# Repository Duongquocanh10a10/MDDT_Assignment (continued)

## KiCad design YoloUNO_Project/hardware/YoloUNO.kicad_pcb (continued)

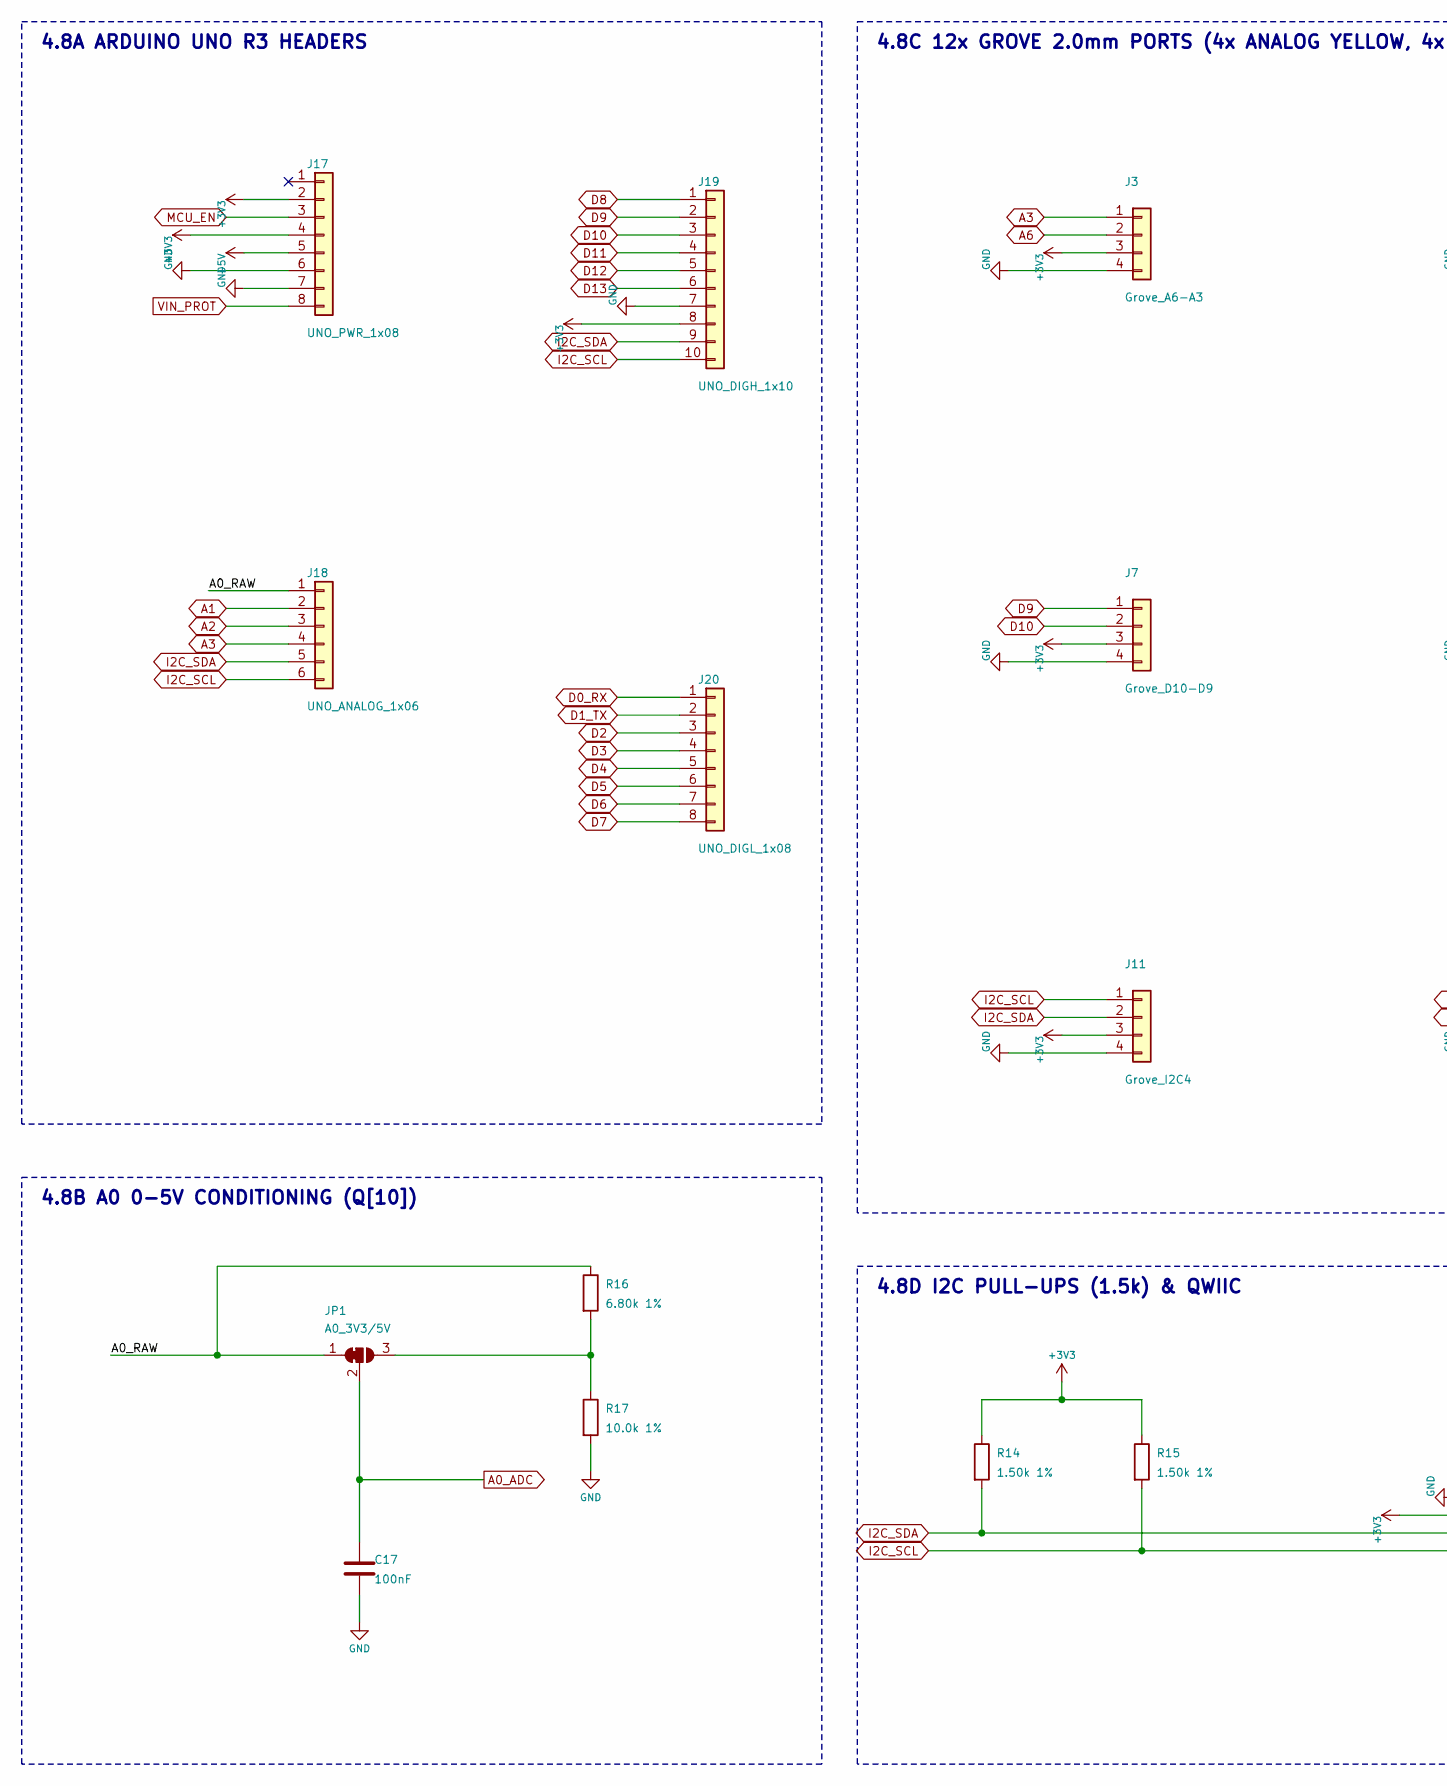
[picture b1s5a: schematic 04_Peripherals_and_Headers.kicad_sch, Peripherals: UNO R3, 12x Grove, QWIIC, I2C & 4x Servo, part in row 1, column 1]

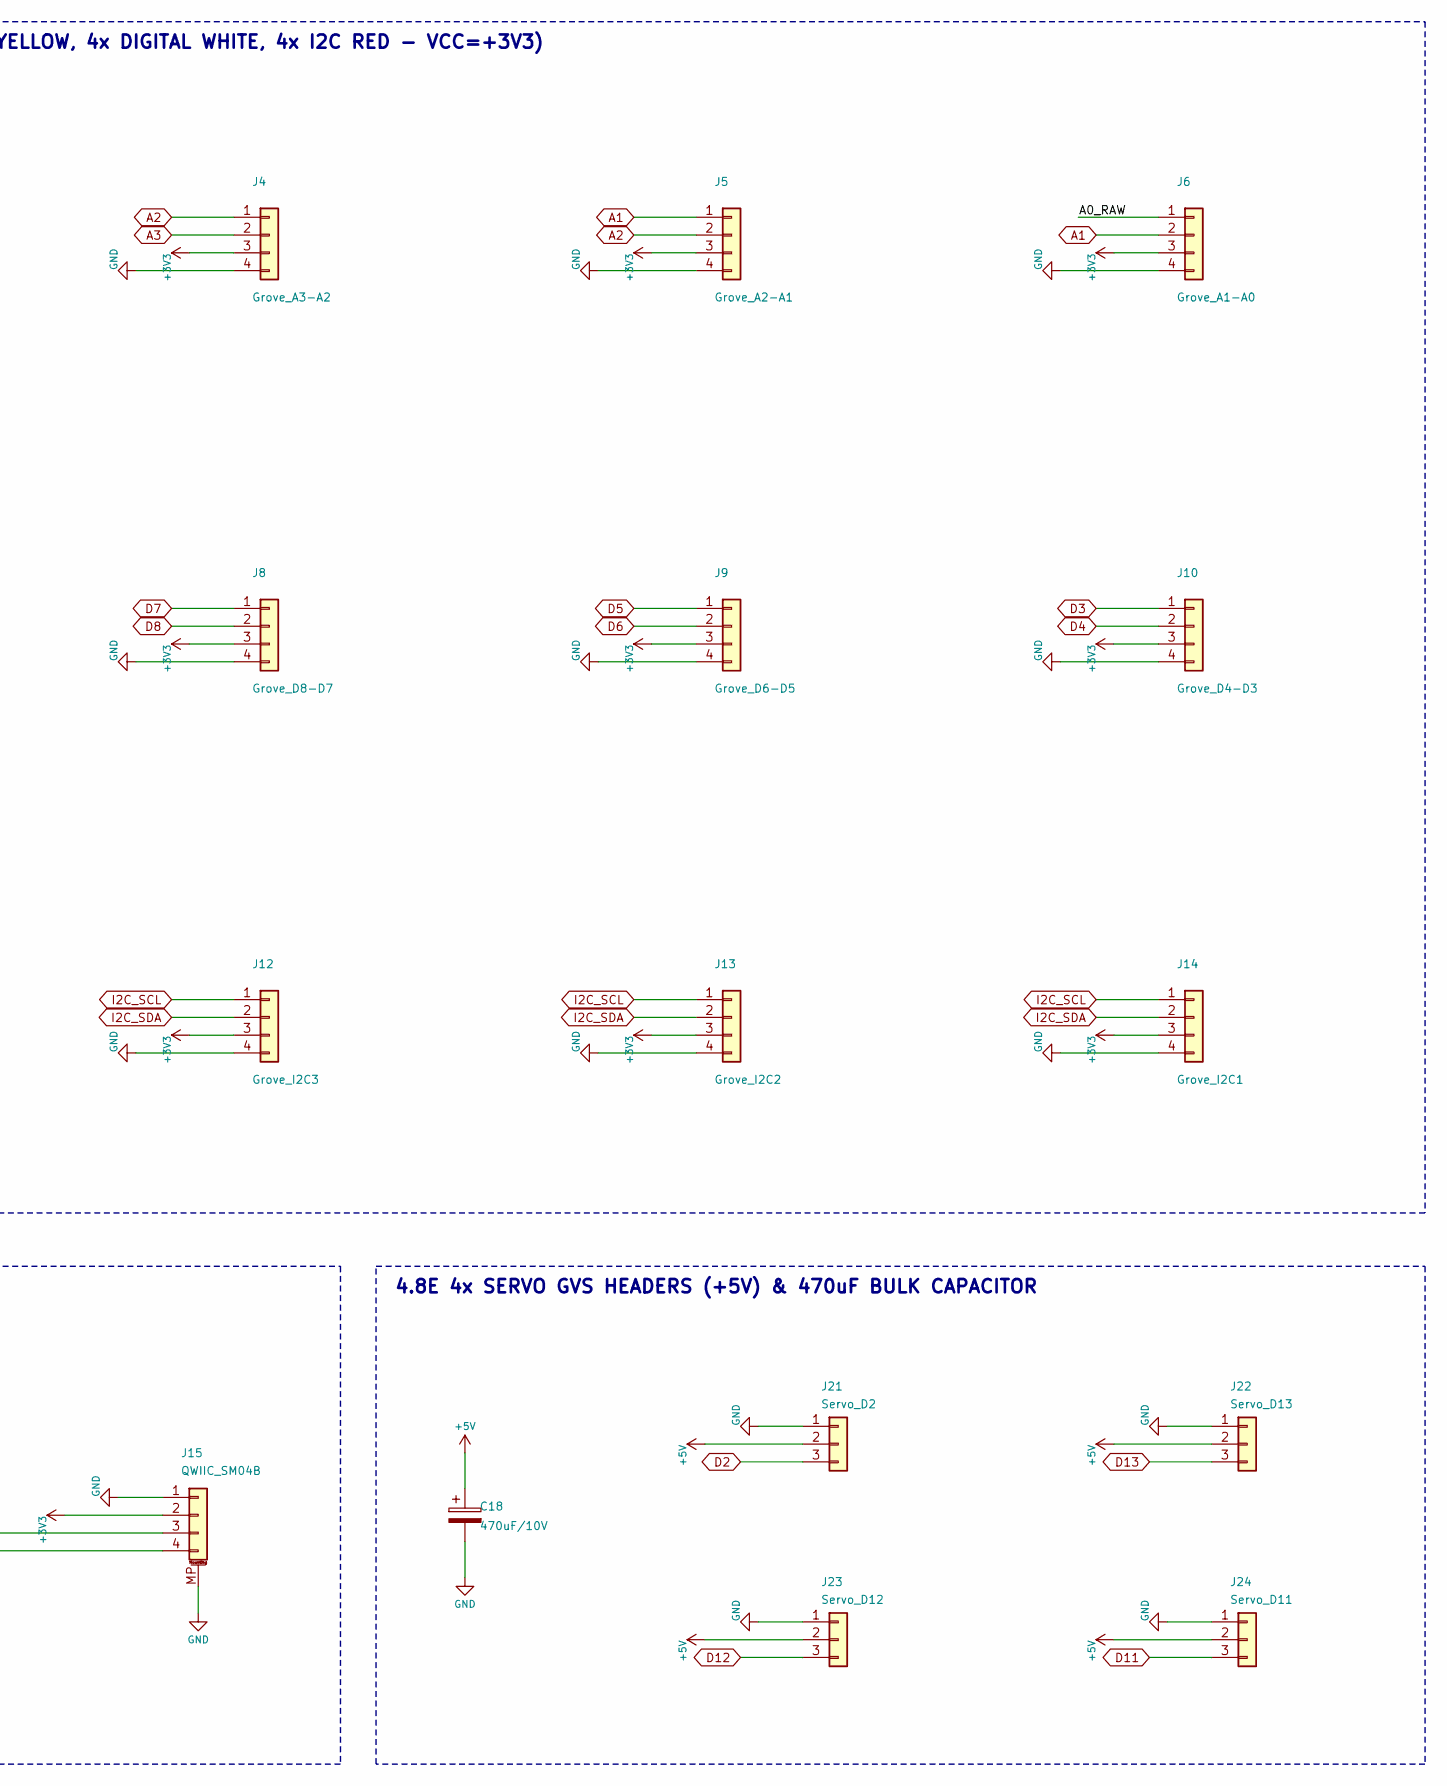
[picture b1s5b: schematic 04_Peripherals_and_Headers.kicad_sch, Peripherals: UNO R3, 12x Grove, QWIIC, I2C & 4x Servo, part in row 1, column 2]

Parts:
C17: 100nF; C_0603_1608Metric; MPN CL10B104KB8NNNC; LCSC C1591
C18: 470uF/10V; CP_Elec_8x10.5; MPN EEE-FK1A471P; LCSC C134734
J3: Grove_A6-A3; NS-Tech_Grove_1x04_P2mm_Vertical; MPN 110990030; LCSC C2906423
J4: Grove_A3-A2; NS-Tech_Grove_1x04_P2mm_Vertical; MPN 110990030; LCSC C2906423
J5: Grove_A2-A1; NS-Tech_Grove_1x04_P2mm_Vertical; MPN 110990030; LCSC C2906423
J6: Grove_A1-A0; NS-Tech_Grove_1x04_P2mm_Vertical; MPN 110990030; LCSC C2906423
J7: Grove_D10-D9; NS-Tech_Grove_1x04_P2mm_Vertical; MPN 112060001; LCSC C492401
J8: Grove_D8-D7; NS-Tech_Grove_1x04_P2mm_Vertical; MPN 112060001; LCSC C492401
J9: Grove_D6-D5; NS-Tech_Grove_1x04_P2mm_Vertical; MPN 112060001; LCSC C492401
J10: Grove_D4-D3; NS-Tech_Grove_1x04_P2mm_Vertical; MPN 112060001; LCSC C492401
J11: Grove_I2C4; NS-Tech_Grove_1x04_P2mm_Vertical; MPN 110990031; LCSC C2906424
J12: Grove_I2C3; NS-Tech_Grove_1x04_P2mm_Vertical; MPN 110990031; LCSC C2906424
J13: Grove_I2C2; NS-Tech_Grove_1x04_P2mm_Vertical; MPN 110990031; LCSC C2906424
J14: Grove_I2C1; NS-Tech_Grove_1x04_P2mm_Vertical; MPN 110990031; LCSC C2906424
J15: QWIIC_SM04B; JST_SH_SM04B-SRSS-TB_1x04-1MP_P1.00mm_Horizontal; MPN SM04B-SRSS-TB; LCSC C160404
J17: UNO_PWR_1x08; PinSocket_1x08_P2.54mm_Vertical; MPN FH-254-1x08; LCSC C49661
J18: UNO_ANALOG_1x06; PinSocket_1x06_P2.54mm_Vertical; MPN FH-254-1x06; LCSC C49659
J19: UNO_DIGH_1x10; PinSocket_1x10_P2.54mm_Vertical; MPN FH-254-1x10; LCSC C49663
J20: UNO_DIGL_1x08; PinSocket_1x08_P2.54mm_Vertical; MPN FH-254-1x08; LCSC C49661
J21: Servo_D2; PinHeader_1x03_P2.54mm_Vertical; MPN X6511WV-1x3; LCSC C492405
J22: Servo_D13; PinHeader_1x03_P2.54mm_Vertical; MPN X6511WV-1x3; LCSC C492405
J23: Servo_D12; PinHeader_1x03_P2.54mm_Vertical; MPN X6511WV-1x3; LCSC C492405
J24: Servo_D11; PinHeader_1x03_P2.54mm_Vertical; MPN X6511WV-1x3; LCSC C492405
JP1: A0_3V3/5V; SolderJumper-3_P1.3mm_Bridged12_Pad1.0x1.5mm; MPN SJ-3-1.3MM; LCSC N/A
R14, R15: 1.50k 1%; R_0603_1608Metric; MPN RC0603FR-071K5L; LCSC C22843
R16: 6.80k 1%; R_0603_1608Metric; MPN RC0603FR-076K8L; LCSC C23212
R17: 10.0k 1%; R_0603_1608Metric; MPN RC0603FR-0710KL; LCSC C25804

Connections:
+3V3: J3.3, J4.3, J5.3, J6.3, J7.3, J8.3, J9.3, J10.3, J11.3, J12.3, J13.3, J14.3, J15.2, J17.2, J17.4, J19.8, R14.1, R15.1; also elsewhere on the board
+5V: C18.1, J17.5, J21.2, J22.2, J23.2, J24.2; also elsewhere on the board
/04_Peripherals_and_Headers/A0_RAW: J6.1, J18.1, JP1.1 (A), R16.1
A0_ADC: C17.1, JP1.2 (C); also elsewhere on the board
A1: J5.1, J6.2, J18.2; also elsewhere on the board
A2: J4.1, J5.2, J18.3; also elsewhere on the board
A3: J3.1, J4.2, J18.4; also elsewhere on the board
A6: J3.2; also elsewhere on the board
D0_RX: J20.1; also elsewhere on the board
D1_TX: J20.2; also elsewhere on the board
D2: J20.3, J21.3; also elsewhere on the board
D3: J10.1, J20.4; also elsewhere on the board
D4: J10.2, J20.5; also elsewhere on the board
D5: J9.1, J20.6; also elsewhere on the board
D6: J9.2, J20.7; also elsewhere on the board
D7: J8.1, J20.8; also elsewhere on the board
D8: J8.2, J19.1; also elsewhere on the board
D9: J7.1, J19.2; also elsewhere on the board
D10: J7.2, J19.3; also elsewhere on the board
D11: J19.4, J24.3; also elsewhere on the board
D12: J19.5, J23.3; also elsewhere on the board
D13: J19.6, J22.3; also elsewhere on the board
I2C_SCL: J11.1, J12.1, J13.1, J14.1, J15.4, J18.6, J19.10, R15.2; also elsewhere on the board
I2C_SDA: J11.2, J12.2, J13.2, J14.2, J15.3, J18.5, J19.9, R14.2; also elsewhere on the board
MCU_EN: J17.3; also elsewhere on the board
unnamed: JP1.3 (B), R16.2, R17.1
VIN_PROT: J17.8; also elsewhere on the board

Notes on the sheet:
4.8A ARDUINO UNO R3 HEADERS
4.8B A0 0-5V CONDITIONING (Q[10])
4.8C 12x GROVE 2.0mm PORTS (4x ANALOG YELLOW, 4x DIGITAL WHITE, 4x I2C RED - VCC=+3V3)
4.8D I2C PULL-UPS (1.5k) & QWIIC
4.8E 4x SERVO GVS HEADERS (+5V) & 470uF BULK CAPACITOR

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
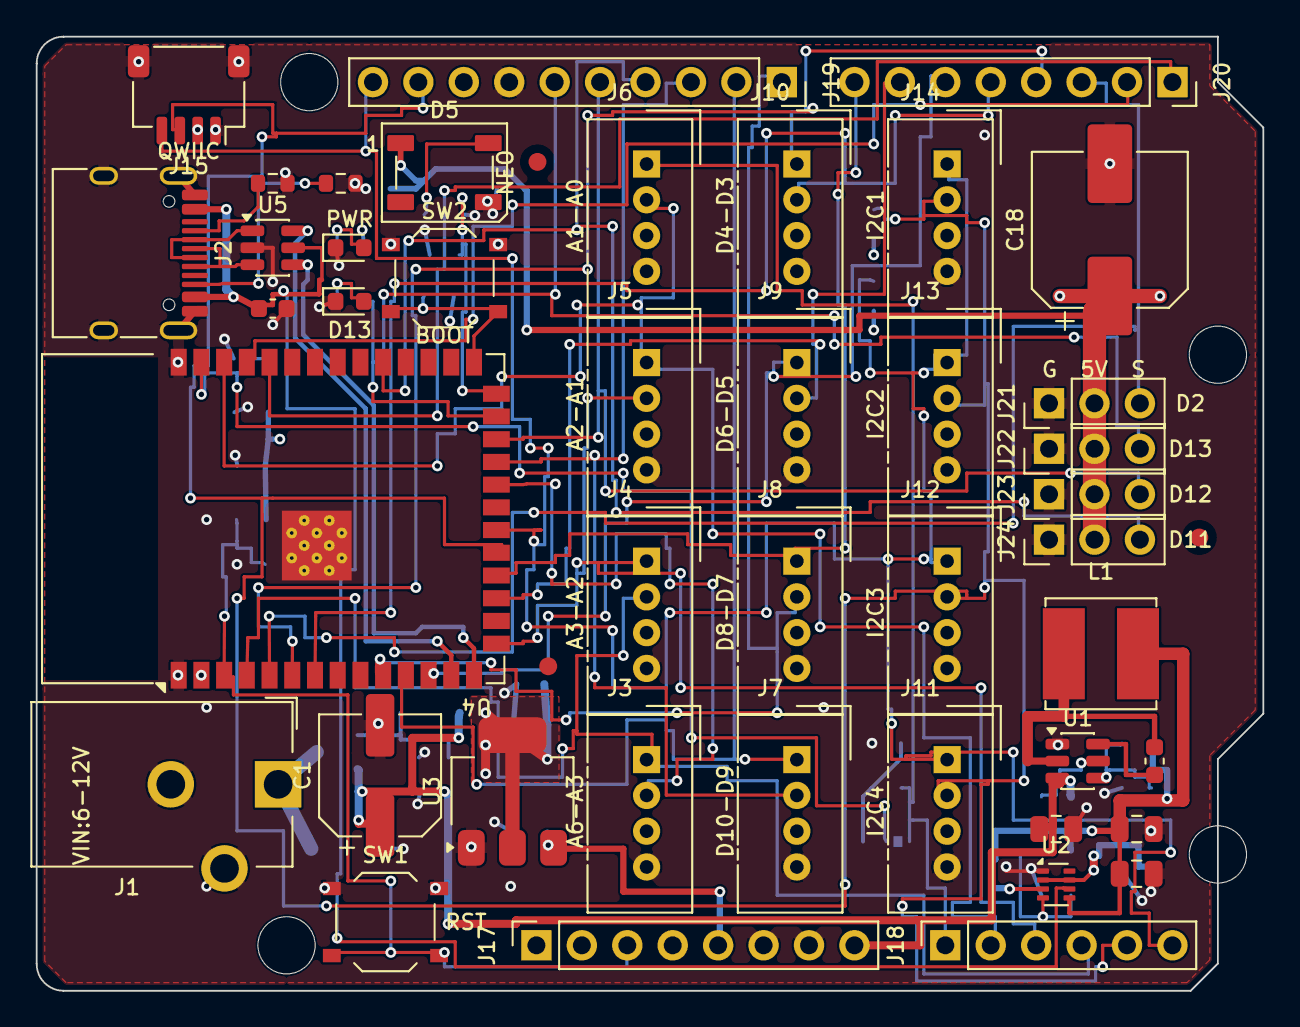
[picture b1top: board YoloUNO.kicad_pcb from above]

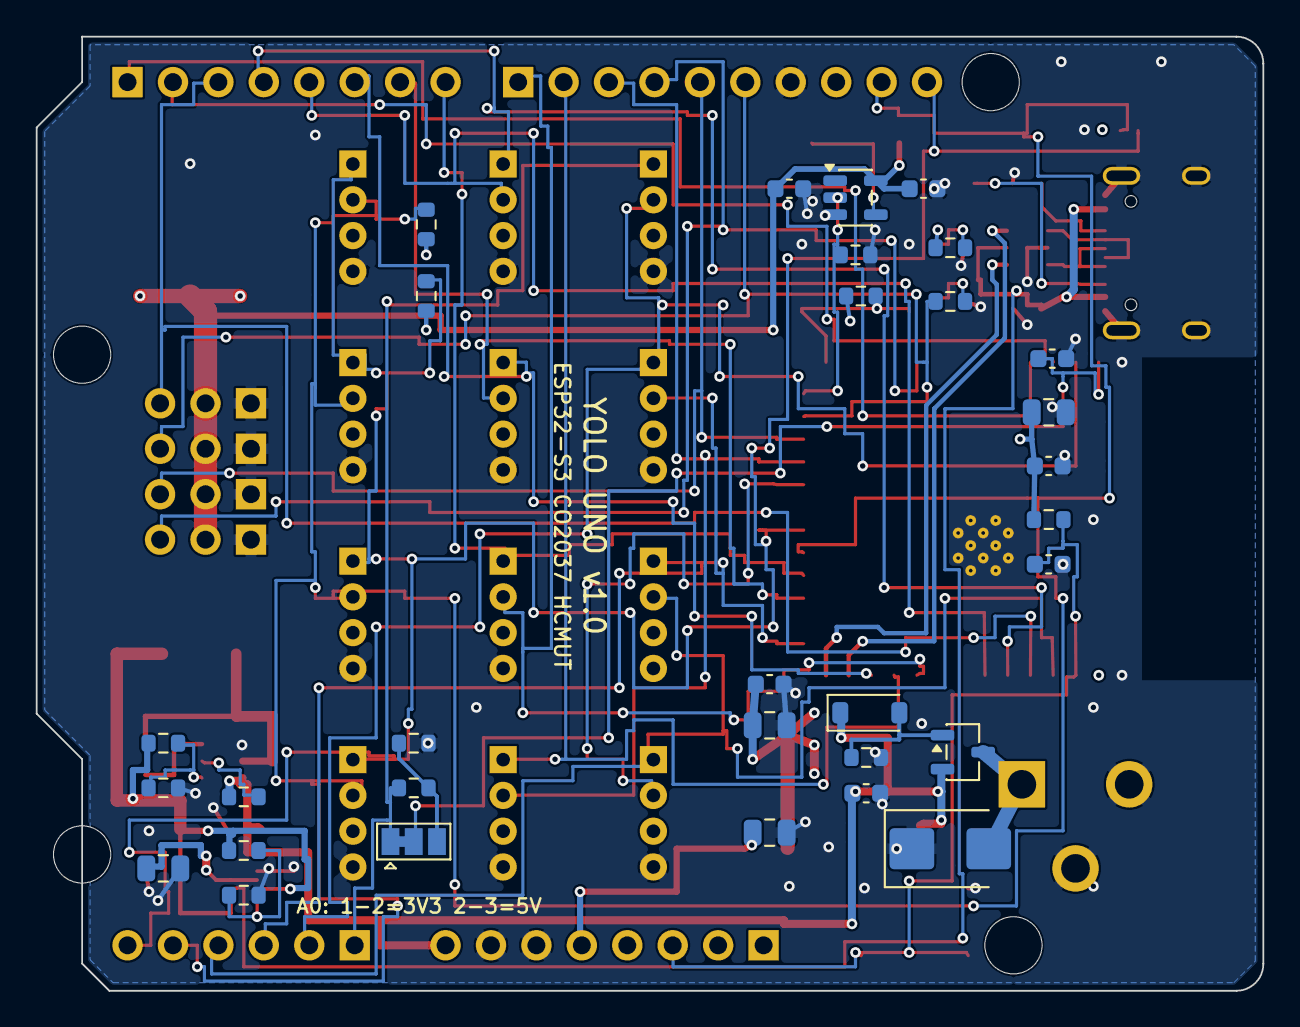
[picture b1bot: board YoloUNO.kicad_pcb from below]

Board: 4 copper layers, 68.6 x 53.3 mm, 81 parts (31 on the bottom side), 48 nets.

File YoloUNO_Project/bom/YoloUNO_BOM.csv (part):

Designator,Quantity,Value,Description,Footprint,Manufacturer,MPN,LCSC_Part,Block,Datasheet_Source
J1,1,PJ-002A (6-12V),DC Barrel Jack 5.5x2.1mm THT (6-12V Input),YoloUNO:BarrelJack_CUI_PJ-102AH_Horizontal,CUI Devices,PJ-002A,C720477,4.1 Input Power & Protection,CUI Devices PJ-002A Datasheet
D1,1,SMBJ15CA,Bidirectional TVS Diode 15V Standoff 600W Surge Clamp,YoloUNO:D_SMB,Littelfuse,SMBJ15CA,C123785,4.1 Input Power & Protection,Littelfuse SMBJ Series Datasheet
Q1,1,AO3407A,"P-Channel MOSFET -30V +/-20V VGS -4.3A RDS(on)<=48mOhm Reverse-Polarity Ideal Diode",YoloUNO:SOT-23-3,Alpha & Omega Semiconductor,AO3407A,C347475,4.1 Input Power & Protection,AOS AO3407A Datasheet
D2,1,BZT52C10 (10V),Zener Diode 10V 500mW Gate-Source Clamp for Q1,YoloUNO:D_SOD-123,Diodes Incorporated,BZT52C10-7-F,C81598,4.1 Input Power & Protection,Diodes Inc. BZT52C Series Datasheet
R1,1,47k 1%,Thick Film Resistor 0603 Q1 Gate Pull-Down,YoloUNO:R_0603_1608Metric,Yageo,RC0603FR-0747KL,C25819,4.1 Input Power & Protection,Yageo RC0603 Datasheet
C1,1,47uF/25V,Aluminum Electrolytic Capacitor SMD 6.3x5.4mm Input Bulk,YoloUNO:CP_Elec_6.3x5.4,Panasonic,EEE-FK1E470P,C72485,4.1 Input Power & Protection,Panasonic EEE-FK Series Datasheet
C2,1,100nF 50V X7R,MLCC Capacitor 0603 Input HF Bypass,YoloUNO:C_0603_1608Metric,Samsung Electro-Mechanics,CL10B104KB8NNNC,C1591,4.1 Input Power & Protection,Samsung CL10B104KB8NNNC Datasheet
U1,1,TPS54202DDCR,4.5-28V Input 2A Synchronous Step-Down Buck Converter 500kHz VFB=0.596V,YoloUNO:SOT-23-6,Texas Instruments,TPS54202DDCR,C128249,4.2 5V Buck Converter,TI TPS54202 Datasheet (SLVSDF5)
C3,1,10uF/25V X5R,MLCC Capacitor 0805 Buck Input Ceramic Cap,YoloUNO:C_0805_2012Metric,Murata,GRM21BR61E106KA73L,C15850,4.2 5V Buck Converter,Murata GRM21BR61E106KA73 Datasheet
C4,1,100nF 50V X7R,MLCC Capacitor 0603 Bootstrap Cap (BOOT-SW),YoloUNO:C_0603_1608Metric,Samsung Electro-Mechanics,CL10B104KB8NNNC,C1591,4.2 5V Buck Converter,Samsung CL10B104KB8NNNC Datasheet
L1,1,15uH (SRN6045),Shielded Power Inductor Isat>=2.9A Irms>=2.5A DCR~65mOhm 6x6mm,YoloUNO:L_Bourns_SRN6045TA,Bourns,SRN6045TA-150M,C169400,4.2 5V Buck Converter,Bourns SRN6045TA Datasheet
R2,1,100k 1%,Thick Film Resistor 0603 Buck EN Pull-Up,YoloUNO:R_0603_1608Metric,Yageo,RC0603FR-07100KL,C25803,4.2 5V Buck Converter,Yageo RC0603 Datasheet
R3,1,68.0k 1%,Thick Film Resistor 0603 Buck Feedback Top,YoloUNO:R_0603_1608Metric,Yageo,RC0603FR-0768KL,C23231,4.2 5V Buck Converter,Yageo RC0603 Datasheet
R4,1,9.10k 1%,Thick Film Resistor 0603 Buck Feedback Bottom,YoloUNO:R_0603_1608Metric,Yageo,RC0603FR-079K1L,C23268,4.2 5V Buck Converter,Yageo RC0603 Datasheet
"C5, C6",2,22uF/16V X5R,MLCC Capacitor 0805 Buck Output Filter (Parallel),YoloUNO:C_0805_2012Metric,Murata,GRM21BR61C226ME44L,C45783,4.2 5V Buck Converter,Murata GRM21BR61C226ME44 Datasheet
U2,1,TPS2116DRLR,1.6-5.5V 2.5A Priority Power Multiplexer Reverse Current Blocking RON=40mOhm,YoloUNO:SOT-583-8,Texas Instruments,TPS2116DRLR,C2875184,4.3 USB/DC Power-Path,TI TPS2116 Datasheet (SLVSFJ9)
R5,1,36.0k 1%,Thick Film Resistor 0603 PR1 Priority Top Divider,YoloUNO:R_0603_1608Metric,Yageo,RC0603FR-0736KL,C23146,4.3 USB/DC Power-Path,Yageo RC0603 Datasheet
R6,1,10.0k 1%,Thick Film Resistor 0603 PR1 Priority Bottom Divider,YoloUNO:R_0603_1608Metric,Yageo,RC0603FR-0710KL,C25804,4.3 USB/DC Power-Path,Yageo RC0603 Datasheet
C7,1,10uF/16V X5R,MLCC Capacitor 0805 +5V Rail Local Decoupling,YoloUNO:C_0805_2012Metric,Samsung Electro-Mechanics,CL21A106KOQNNNE,C17024,4.3 USB/DC Power-Path,Samsung CL21A106KOQNNNE Datasheet
U3,1,AP2114H-3.3TRG1,1.0A Low-Noise CMOS LDO Regulator VDO=450mV typ IQ=60uA typ,YoloUNO:SOT-223-3_TabPin2,Diodes Incorporated,AP2114H-3.3TRG1,C151275,4.4 3.3V LDO Regulator,Diodes Inc. AP2114 Datasheet
C8,1,10uF/16V X5R,MLCC Capacitor 0805 LDO Input Decoupling,YoloUNO:C_0805_2012Metric,Samsung Electro-Mechanics,CL21A106KOQNNNE,C17024,4.4 3.3V LDO Regulator,Samsung CL21A106KOQNNNE Datasheet
C9,1,22uF/16V X5R,MLCC Capacitor 0805 LDO Output Decoupling,YoloUNO:C_0805_2012Metric,Murata,GRM21BR61C226ME44L,C45783,4.4 3.3V LDO Regulator,Murata GRM21BR61C226ME44 Datasheet
C10,1,100nF 50V X7R,MLCC Capacitor 0603 LDO Output HF Bypass,YoloUNO:C_0603_1608Metric,Samsung Electro-Mechanics,CL10B104KB8NNNC,C1591,4.4 3.3V LDO Regulator,Samsung CL10B104KB8NNNC Datasheet
D3,1,PWR_GREEN,0603 SMD Green LED Power Indicator (+3V3),YoloUNO:LED_0603_1608Metric,Everlight Electronics,19-217/GHC-YR1S2/3T,C72043,4.4 3.3V LDO Regulator,Everlight 19-217/GHC Datasheet
R11,1,470R 1%,Thick Film Resistor 0603 PWR LED Current Limiting (2.55mA),YoloUNO:R_0603_1608Metric,Yageo,RC0603FR-07470RL,C23179,4.4 3.3V LDO Regulator,Yageo RC0603 Datasheet
U4,1,ESP32-S3-WROOM-1-N16R8,Dual-Core Xtensa LX7 240MHz Wi-Fi/BLE 5 16MB Flash 8MB Octal PSRAM PCB Ant,YoloUNO:ESP32-S3-WROOM-1,Espressif Systems,ESP32-S3-WROOM-1-N16R8,C2913202,4.5 MCU ESP32-S3,Espressif ESP32-S3-WROOM-1 Datasheet
C11,1,22uF/16V X5R,MLCC Capacitor 0805 MCU 3V3 Bulk Decoupling,YoloUNO:C_0805_2012Metric,Murata,GRM21BR61C226ME44L,C45783,4.5 MCU ESP32-S3,Murata GRM21BR61C226ME44 Datasheet
C12,1,100nF 50V X7R,MLCC Capacitor 0603 MCU 3V3 HF Bypass,YoloUNO:C_0603_1608Metric,Samsung Electro-Mechanics,CL10B104KB8NNNC,C1591,4.5 MCU ESP32-S3,Samsung CL10B104KB8NNNC Datasheet
R7,1,10.0k 1%,Thick Film Resistor 0603 EN Pull-Up to +3V3,YoloUNO:R_0603_1608Metric,Yageo,RC0603FR-0710KL,C25804,4.5 MCU ESP32-S3,Yageo RC0603 Datasheet
C13,1,1uF/16V X7R,MLCC Capacitor 0603 EN RC Delay Cap (tau=10ms),YoloUNO:C_0603_1608Metric,Samsung Electro-Mechanics,CL10B105KO8NNNC,C15849,4.5 MCU ESP32-S3,Samsung CL10B105KO8NNNC Datasheet
"SW1, SW2",2,TS-1187A-B-A-B,SMD Tactile Push Button Switch 5.1x5.1mm (RESET & BOOT),YoloUNO:SW_Push_1P1T_XKB_TS-1187A,XKB Connectivity,TS-1187A-B-A-B,C318884,4.5 MCU ESP32-S3,XKB TS-1187A Datasheet
R8,1,10.0k 1%,Thick Film Resistor 0603 GPIO0 BOOT Pull-Up,YoloUNO:R_0603_1608Metric,Yageo,RC0603FR-0710KL,C25804,4.5 MCU ESP32-S3,Yageo RC0603 Datasheet
J2,1,USB_C_16P,USB 2.0 Type-C 16-Pin Receptacle SMD,YoloUNO:USB_C_Receptacle_HRO_TYPE-C-31-M-12,Korean Hroparts Elec,TYPE-C-31-M-12,C165948,4.6 USB Type-C & ESD,HRO TYPE-C-31-M-12 Datasheet
"R9, R10",2,5.10k 1%,Thick Film Resistor 0603 CC1 & CC2 Independent Rd Pull-Downs,YoloUNO:R_0603_1608Metric,Yageo,RC0603FR-075K1L,C23186,4.6 USB Type-C & ESD,Yageo RC0603 Datasheet
U5,1,USBLC6-2SC6,Ultra-Low Capacitance 2.5pF USB 2.0 ESD Protection Array,YoloUNO:SOT-23-6,STMicroelectronics,USBLC6-2SC6,C7519,4.6 USB Type-C & ESD,ST USBLC6-2SC6 Datasheet
C14,1,100nF 50V X7R,MLCC Capacitor 0603 VBUS ESD Local Bypass,YoloUNO:C_0603_1608Metric,Samsung Electro-Mechanics,CL10B104KB8NNNC,C1591,4.6 USB Type-C & ESD,Samsung CL10B104KB8NNNC Datasheet
D4,1,D13_RED,0603 SMD Red LED User D13 Indicator (GPIO48),YoloUNO:LED_0603_1608Metric,Everlight Electronics,19-217/R6C-AL1M2VY/3T,C2286,4.7 Display LED & NeoPixel,Everlight 19-217/R6C Datasheet
R12,1,270R 1%,Thick Film Resistor 0603 D13 LED Current Limiting (4.81mA),YoloUNO:R_0603_1608Metric,Yageo,RC0603FR-07270RL,C22966,4.7 Display LED & NeoPixel,Yageo RC0603 Datasheet
R13,1,10.0k (Strap PD),Thick Film Resistor 0603 GPIO45 Strapping Safety Pull-Down,YoloUNO:R_0603_1608Metric,Yageo,RC0603FR-0710KL,C25804,4.7 Display LED & NeoPixel,Yageo RC0603 Datasheet
U6,1,SN74LV1T34DBVR,Single Power-Supply CMOS Buffer 3.3V to 5V Level Shifter,YoloUNO:SOT-23-5,Texas Instruments,SN74LV1T34DBVR,C100018,4.7 Display LED & NeoPixel,TI SN74LV1T34 Datasheet
C15,1,100nF 50V X7R,MLCC Capacitor 0603 U6 +5V Bypass,YoloUNO:C_0603_1608Metric,Samsung Electro-Mechanics,CL10B104KB8NNNC,C1591,4.7 Display LED & NeoPixel,Samsung CL10B104KB8NNNC Datasheet
D5,1,WS2812B-B,Addressable RGB NeoPixel LED 5050 +5V Powered,YoloUNO:LED_WS2812B_PLCC4_5.0x5.0mm_P3.2mm,Worldsemi,WS2812B-B/W,C114586,4.7 Display LED & NeoPixel,Worldsemi WS2812B Datasheet
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
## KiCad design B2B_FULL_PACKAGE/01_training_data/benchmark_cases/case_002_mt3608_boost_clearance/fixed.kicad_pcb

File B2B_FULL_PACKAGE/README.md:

# 📚 Multi-Domain PCB DRC & High-Speed SI/PI AI Training Dataset (v2.0)

**Framework:** Enterprise EDA Autonomous Routing & Signal Integrity Dataset
**Standard:** IPC-2221 Class 2 & IPC-2141 Controlled Impedance
**Total Assets:** 371 curated files | 18 physics-grounded benchmark cases | 31 milestone PCB models | 84 KiCad DRC logs

---

## 1. Executive Summary & Domain Diversity

This enterprise training dataset provides full geometric, electrical, and topological annotations for training Graph Neural Networks (GNNs), reinforcement learning agents, and algorithmic autorouters on multi-layer PCB layout optimization.

### Multi-Domain Coverage (18 Distinct Benchmark Cases):
1. **High-Speed Signal Integrity (SI):**
   - USB 2.0 Differential Pair ($90\Omega \pm 10\%$, skew equalized with serpentine delay meanders)
   - PCIe Gen2 Differential Bus ($100\Omega$, $5	ext{ Gbps}$ phase tuning with trombone matching)
   - High-Frequency Clock Return Path Discontinuity (RPD) bridging across ground split slots
   - High-frequency 3W aggressor crosstalk suppression with GCPW via-stitched guard rings
2. **Power Integrity & Thermal Distribution (PI):**
   - 1.2V Core PDN Target Impedance ($Z_{target} \le 18	ext{ m}\Omega$) and mounting loop inductance
   - Switching inductor thermal spoke starvation prevention under 2.5A continuous DC load
   - Decoupling capacitor loop inductance hierarchy (0201 high-frequency local to bulk)
3. **Mixed-Signal & RF Isolation:**
   - 2.4GHz RF antenna keepout zone copper exclusion and ground plane perimeter edge fencing
   - Star-ground Kelvin bridge split between sensitive analog and noisy digital ground domains
4. **DFM & Assembly Yield:**
   - QFN-28 exposed center pad solder wicking prevention via micro-tented thermal vias

---

## 2. File Organization
- `01_training_data/`: 12 DRC benchmark pairs, 31 milestone progression boards, 84 DRC reports, 28 DRC JSONs.
- `02_algorithms_and_scripts/`: Multi-core parallel router, McMurchie-Ebeling Negotiated Congestion ripup-reroute, Bentley-Ottmann $O((N+K)\log N)$ clearance checker, FSM solver, 66 CAD diagnostics.
- `03_research_documentation/`: Formal topological proofs and mathematical theorems.
- `04_high_speed_si_pi_dataset/`: 6 dedicated transmission line cases, IPC-2141 physics reports, and GNN graph tensors.

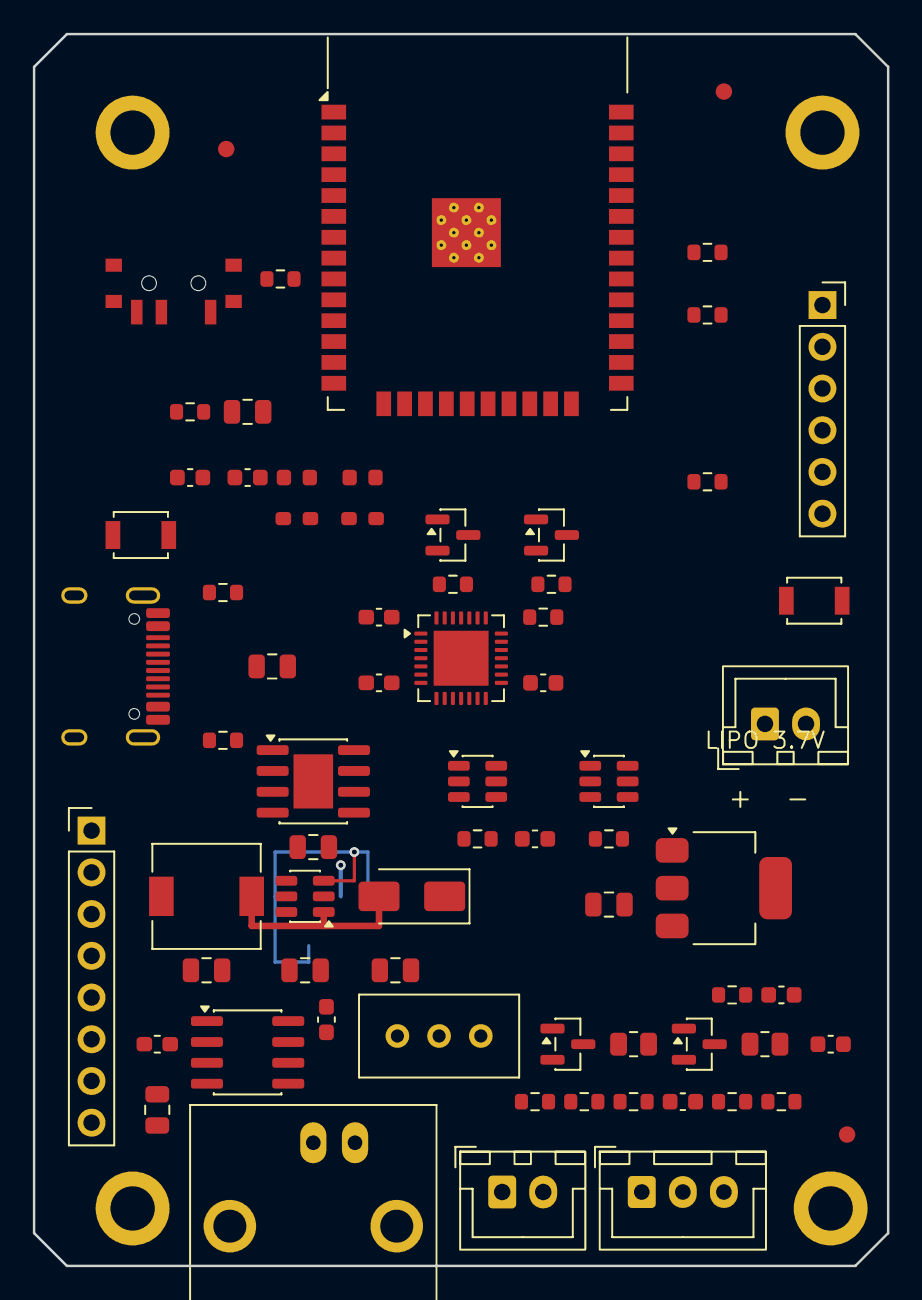
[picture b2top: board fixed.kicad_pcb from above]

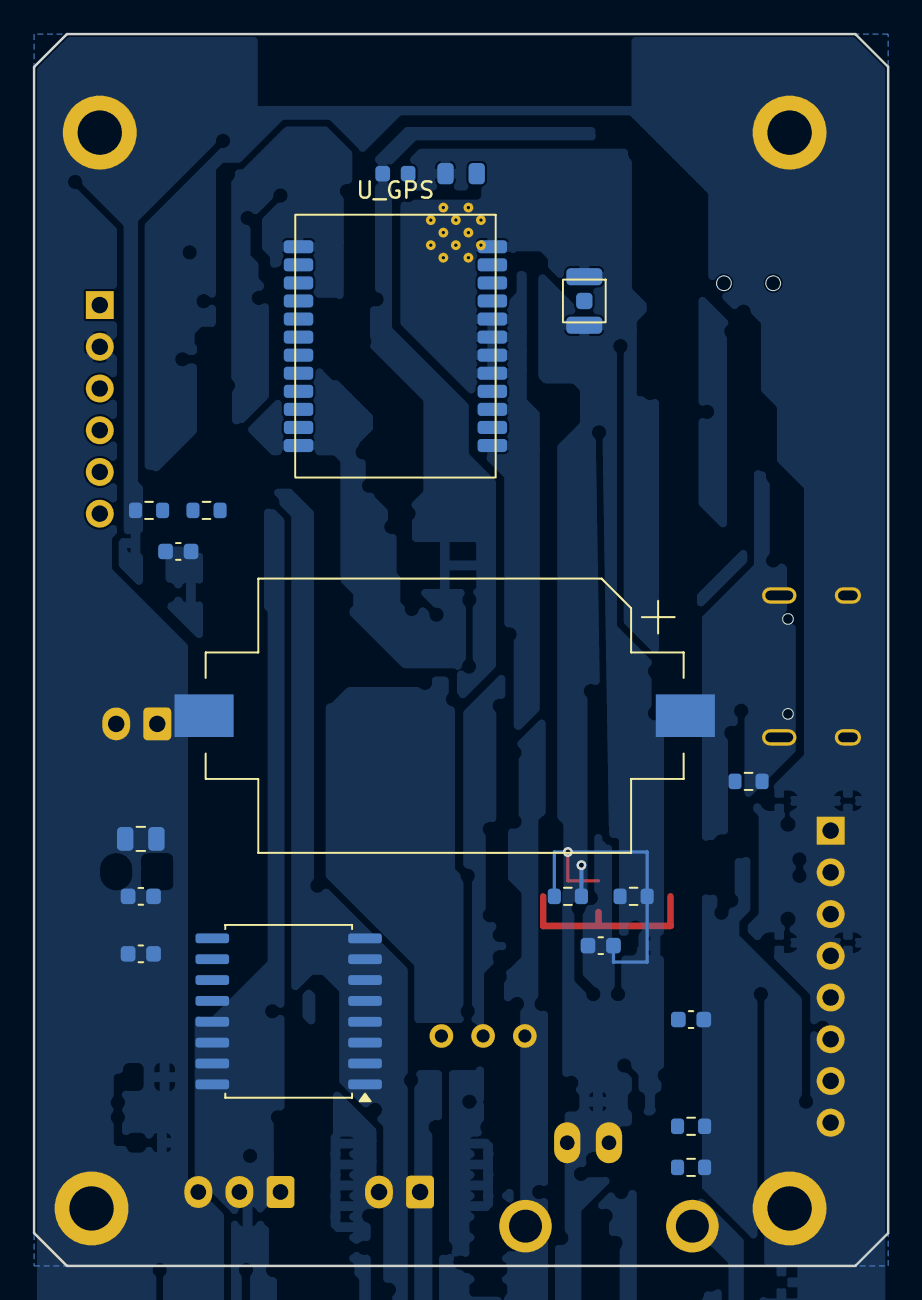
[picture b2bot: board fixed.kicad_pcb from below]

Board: 4 copper layers, 52.0 x 75.0 mm, 94 parts (19 on the bottom side), 62 nets.

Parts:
BT1: CR2032; BatteryHolder_Keystone_1060_1x2032
C_ANA_BULK: 10uF; C_0805_2012Metric
C_BAT_ADC: 100nF; C_0603_1608Metric
C_BAT_CHG: 10uF; C_0805_2012Metric
C_BST_IN: 22uF; C_0805_2012Metric
C_BST_OUT1, C_BST_OUT2: 22uF; C_0805_2012Metric
C_CP_DEC: 100nF; C_0603_1608Metric
C_CP_VDD: 4.7uF; C_0603_1608Metric
C_CP_VREG: 4.7uF; C_0603_1608Metric
C_DS_VCC: 100nF; C_0603_1608Metric
C_EN: 100nF; C_0603_1608Metric
C_FF: 22pF; C_0603_1608Metric
C_GPS1: 100nF; C_0603_1608Metric
C_GPS2: 10uF; C_0805_2012Metric
C_LCD_VCC: 100nF; C_0603_1608Metric
C_LDO_DEC: 100nF; C_0603_1608Metric
C_LDO_IN: 10uF; C_0805_2012Metric
C_LDO_OUT: 22uF; C_0805_2012Metric
C_MCU_BULK: 10uF; C_0805_2012Metric
C_MCU_DEC: 100nF; C_0603_1608Metric
C_PH_FILT: 100nF; C_0603_1608Metric
C_RTC_VCC: 100nF; C_0603_1608Metric
C_TDS_FILT: 100nF; C_0603_1608Metric
C_U9_VCC: 100nF; C_0603_1608Metric
C_VBUS: 10uF; C_0805_2012Metric
C_VDD: 100nF; C_0603_1608Metric
D1: SS34; D_SMA
D_CHRG: CHRG; LED_0603_1608Metric
D_STDBY: STDBY; LED_0603_1608Metric
FB1: Ferrite_Bead; L_0603_1608Metric
FID1, FID2, FID3: FID; Fiducial_1mm_Mask2mm
H1, H2, H3, H4: M2.5; MountingHole_2.7mm_M2.5_Pad
J_ANT: U.FL; U.FL_Hirose_U.FL-R-SMT-1_Vertical
J_BAT: LIPO 3.7V; JST_XH_B2B-XH-A_1x02_P2.50mm_Vertical
J_BNC: BNC_pH; BNC_Amphenol_B6252HB-NPP3G-50_Horizontal
J_BOOT: BOOT/UART; PinHeader_1x06_P2.54mm_Vertical
J_LCD: TFT_LCD; PinHeader_1x08_P2.54mm_Vertical
J_TDS: TDS; JST_XH_B2B-XH-A_1x02_P2.50mm_Vertical
J_TEMP: DS18B20; JST_XH_B3B-XH-A_1x03_P2.50mm_Vertical
J_USB: USB-C; USB_C_Receptacle_HRO_TYPE-C-31-M-12
L1: 2.2uH; L_6.3x6.3_H3
Q1: 2N7002_TDS; SOT-23
Q2: 2N7002_LCD; SOT-23
Q3, Q4: MMBT3904; SOT-23
RV1: 10k_OFFSET; Potentiometer_Bourns_3296W_Vertical
R_BAT1, R_BAT2: 100k; R_0603_1608Metric
R_BL_LIM: 15R; R_0805_2012Metric
R_CC1, R_CC2: 5.1k; R_0603_1608Metric
R_CHRG: 1k; R_0603_1608Metric
R_CP_RST: 10k; R_0603_1608Metric
R_CS: 1k; R_0603_1608Metric
R_DS_PU: 4.7k; R_0603_1608Metric
R_DTR: 10k; R_0603_1608Metric
R_EN: 10k; R_0603_1608Metric
R_FB1: 22k; R_0603_1608Metric
R_FB2: 3.0k; R_0603_1608Metric
R_IO0: 10k; R_0603_1608Metric
R_LCD_GATE: 1k; R_0603_1608Metric
R_LCD_PD: 100k; R_0603_1608Metric
R_PH_BIAS: 10k; R_0603_1608Metric
R_PH_FILT: 1k; R_0603_1608Metric
R_PROG: 2.4k; R_0603_1608Metric
R_RTC_PU: 10k; R_0603_1608Metric
R_RTS: 10k; R_0603_1608Metric
R_SCL_PU: 4.7k; R_0603_1608Metric
R_SDA_PU: 4.7k; R_0603_1608Metric
R_STDBY: 1k; R_0603_1608Metric
R_TDS_FILT: 1k; R_0603_1608Metric
R_TDS_GATE: 1k; R_0603_1608Metric
R_TDS_PD: 100k; R_0603_1608Metric
R_TDS_REF: 1k_1%; R_0805_2012Metric
R_VDD: 100R; R_0603_1608Metric
SW1: ON/OFF; SW_SPDT_PCM12
SW_BOOT: BOOT; SW_SPST_B3U-1000P
SW_EN: RESET; SW_SPST_B3U-1000P
U1: TP4056; SOIC-8-1EP_3.9x4.9mm_P1.27mm_EP2.41x3.3mm
U2: DW01A; SOT-23-6
U3: FS8205A; SOT-23-6
U4: MT3608; SOT-23-6
U5: AMS1117; SOT-223-3_TabPin2
U6: ESP32; ESP32-WROOM-32
U7: DS3231; SOIC-16W_7.5x10.3mm_P1.27mm
U8: CP2102N; QFN-28-1EP_5x5mm_P0.5mm_EP3.35x3.35mm
U9: MCP6002; SOIC-8_3.9x4.9mm_P1.27mm
U_GPS: NEO-M8N; u-blox_NEO

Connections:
+3V3: C_DS_VCC.1, C_GPS1.1, C_GPS2.1, C_LCD_VCC.1, C_LDO_DEC.1, C_LDO_OUT.1, C_MCU_BULK.1, C_MCU_DEC.1, C_RTC_VCC.1, J_BOOT.1, J_LCD.2, J_TEMP.3, R_DS_PU.2, R_EN.2, R_IO0.2, R_RTC_PU.2, R_SCL_PU.2, R_SDA_PU.2, R_TDS_REF.2, U5.2, U6.2, U7.2, U_GPS.22, U_GPS.23
+5V: C_BST_OUT1.1, C_BST_OUT2.1, C_FF.1, C_LDO_IN.1, D1.1, FB1.1, R_FB1.1, U5.3
+5V_ANA: C_ANA_BULK.1, C_U9_VCC.1, FB1.2, RV1.1, U9.8
BAT_MONITOR: C_BAT_ADC.1, R_BAT1.2, R_BAT2.1, U6.5
BST_FB: C_FF.2, R_FB1.2, R_FB2.1, U4.3
B_MINUS: C_VDD.2, J_BAT.2, U2.6, U3.3
CC1: J_USB.A5, R_CC1.1
CC2: J_USB.B5, R_CC2.1
CHIP_PU: C_EN.1, J_BOOT.6, Q4.3, R_EN.1, SW_EN.1, U6.3
CHRG_ANODE: D_CHRG.2, R_CHRG.2
CHRG_LED: D_CHRG.1, U1.7
CP_DTR: Q4.2, R_DTR.1, U8.28
CP_RST: R_CP_RST.2, U8.9
CP_RTS: Q3.2, R_RTS.1, U8.24
CP_VDD: C_CP_DEC.1, C_CP_VDD.1, R_CP_RST.1, U8.6
DRAIN_U3: U3.1, U3.6
DW01_CS: R_CS.2, U2.2
DW01_VDD: C_VDD.1, R_VDD.2, U2.5
GND: BT1.2, C_ANA_BULK.2, C_BAT_ADC.2, C_BAT_CHG.2, C_BST_IN.2, C_BST_OUT1.2, C_BST_OUT2.2, C_CP_DEC.2, C_CP_VDD.2, C_CP_VREG.2, C_DS_VCC.2, C_EN.2, C_GPS1.2, C_GPS2.2, C_LCD_VCC.2, C_LDO_DEC.2, C_LDO_IN.2, C_LDO_OUT.2, C_MCU_BULK.2, C_MCU_DEC.2, C_PH_FILT.2, C_RTC_VCC.2, C_TDS_FILT.2, C_U9_VCC.2, C_VBUS.2, H1.1, H2.1, H3.1, H4.1, J_ANT.2, J_BOOT.2, J_LCD.1, J_TEMP.1, J_USB.A1, J_USB.A12, J_USB.B1, J_USB.B12, J_USB.SH, Q1.2, Q2.2, RV1.3, R_BAT2.2, R_CC1.2, R_CC2.2, R_CS.1, R_FB2.2, R_LCD_PD.2, R_PROG.2, R_TDS_PD.2, SW_BOOT.2, SW_EN.2, U1.1, U1.3, U1.9, U3.2, U4.2, U4.6, U5.1, U6.1, U6.15, U6.38, U6.39, U7.5, U7.6, U7.7, U7.8, U7.9, U7.10, U7.11, U7.12, U7.13, U8.3, U8.29, U9.4, U9.5, U_GPS.1, U_GPS.5, U_GPS.6, U_GPS.7, U_GPS.8, U_GPS.10, U_GPS.12, U_GPS.13, U_GPS.24
GPS_ANT: J_ANT.1, U_GPS.4
GPS_RX: U6.13, U_GPS.20
GPS_TX: U6.16, U_GPS.21
I2C_SCL: R_SCL_PU.1, U6.36, U7.16
I2C_SDA: R_SDA_PU.1, U6.33, U7.15
IO0: J_BOOT.5, Q3.3, R_IO0.1, SW_BOOT.1, U6.25
LCD_BL_PWM: R_LCD_GATE.1, U6.8
LCD_BL_SINK: Q2.3, R_BL_LIM.1
LCD_CS: J_LCD.7, U6.29
LCD_DC: J_LCD.6, U6.27
LCD_GATE: Q2.1, R_LCD_GATE.2, R_LCD_PD.1
LCD_LED_K: J_LCD.8, R_BL_LIM.2
LCD_RST: J_LCD.5, U6.28
LM358B_OUT: U9.6, U9.7
N_Q3_B: Q3.1, R_DTR.2
N_Q4_B: Q4.1, R_RTS.2
OC_GATE: U2.3, U3.4
OD_GATE: U2.1, U3.5
ONEWIRE_TEMP: J_TEMP.2, R_DS_PU.1, U6.26
PH_ADC: C_PH_FILT.1, R_PH_FILT.2, U6.6
PH_AMP_OUT: R_PH_FILT.1, U9.1, U9.2
PH_OFFSET: J_BNC.2, RV1.2, R_PH_BIAS.1
PH_SIGNAL: J_BNC.1, R_PH_BIAS.2, U9.3
RTC_INT: R_RTC_PU.1, U6.9, U7.3
RX0: J_BOOT.4, U6.34, U8.26
SPI_MOSI: J_LCD.4, U6.37
SPI_SCK: J_LCD.3, U6.30
STDBY_ANODE: D_STDBY.2, R_STDBY.2
STDBY_LED: D_STDBY.1, U1.6
SW_NODE: D1.2, L1.2, U4.1
TDS_ADC: C_TDS_FILT.1, R_TDS_FILT.2, U6.7
TDS_GATE: Q1.1, R_TDS_GATE.2, R_TDS_PD.1
TDS_PROBE_DRIVE: J_TDS.1, Q1.3
TDS_PWR_CTRL: R_TDS_GATE.1, U6.11
TDS_SENSE: J_TDS.2, R_TDS_FILT.1, R_TDS_REF.1
TX0: J_BOOT.3, U6.35, U8.25
U1_PROG: R_PROG.1, U1.2
USB_D+: J_USB.A6, J_USB.B6, U8.4
USB_D-: J_USB.A7, J_USB.B7, U8.5
VBAT_RAW: C_BAT_CHG.1, J_BAT.1, R_VDD.1, SW1.3, U1.5
VBAT_RTC: BT1.1, U7.14
VBAT_SW: C_BST_IN.1, L1.1, R_BAT1.1, SW1.2, U4.4, U4.5
VBUS: C_CP_VREG.1, C_VBUS.1, J_USB.A4, J_USB.A9, J_USB.B4, J_USB.B9, R_CHRG.1, R_STDBY.1, U1.4, U1.8, U8.7, U8.8
